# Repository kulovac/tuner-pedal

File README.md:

# Tuner Pedal

A tuner pedal project using an STM32 microcontroller with the CMSIS-DSP library

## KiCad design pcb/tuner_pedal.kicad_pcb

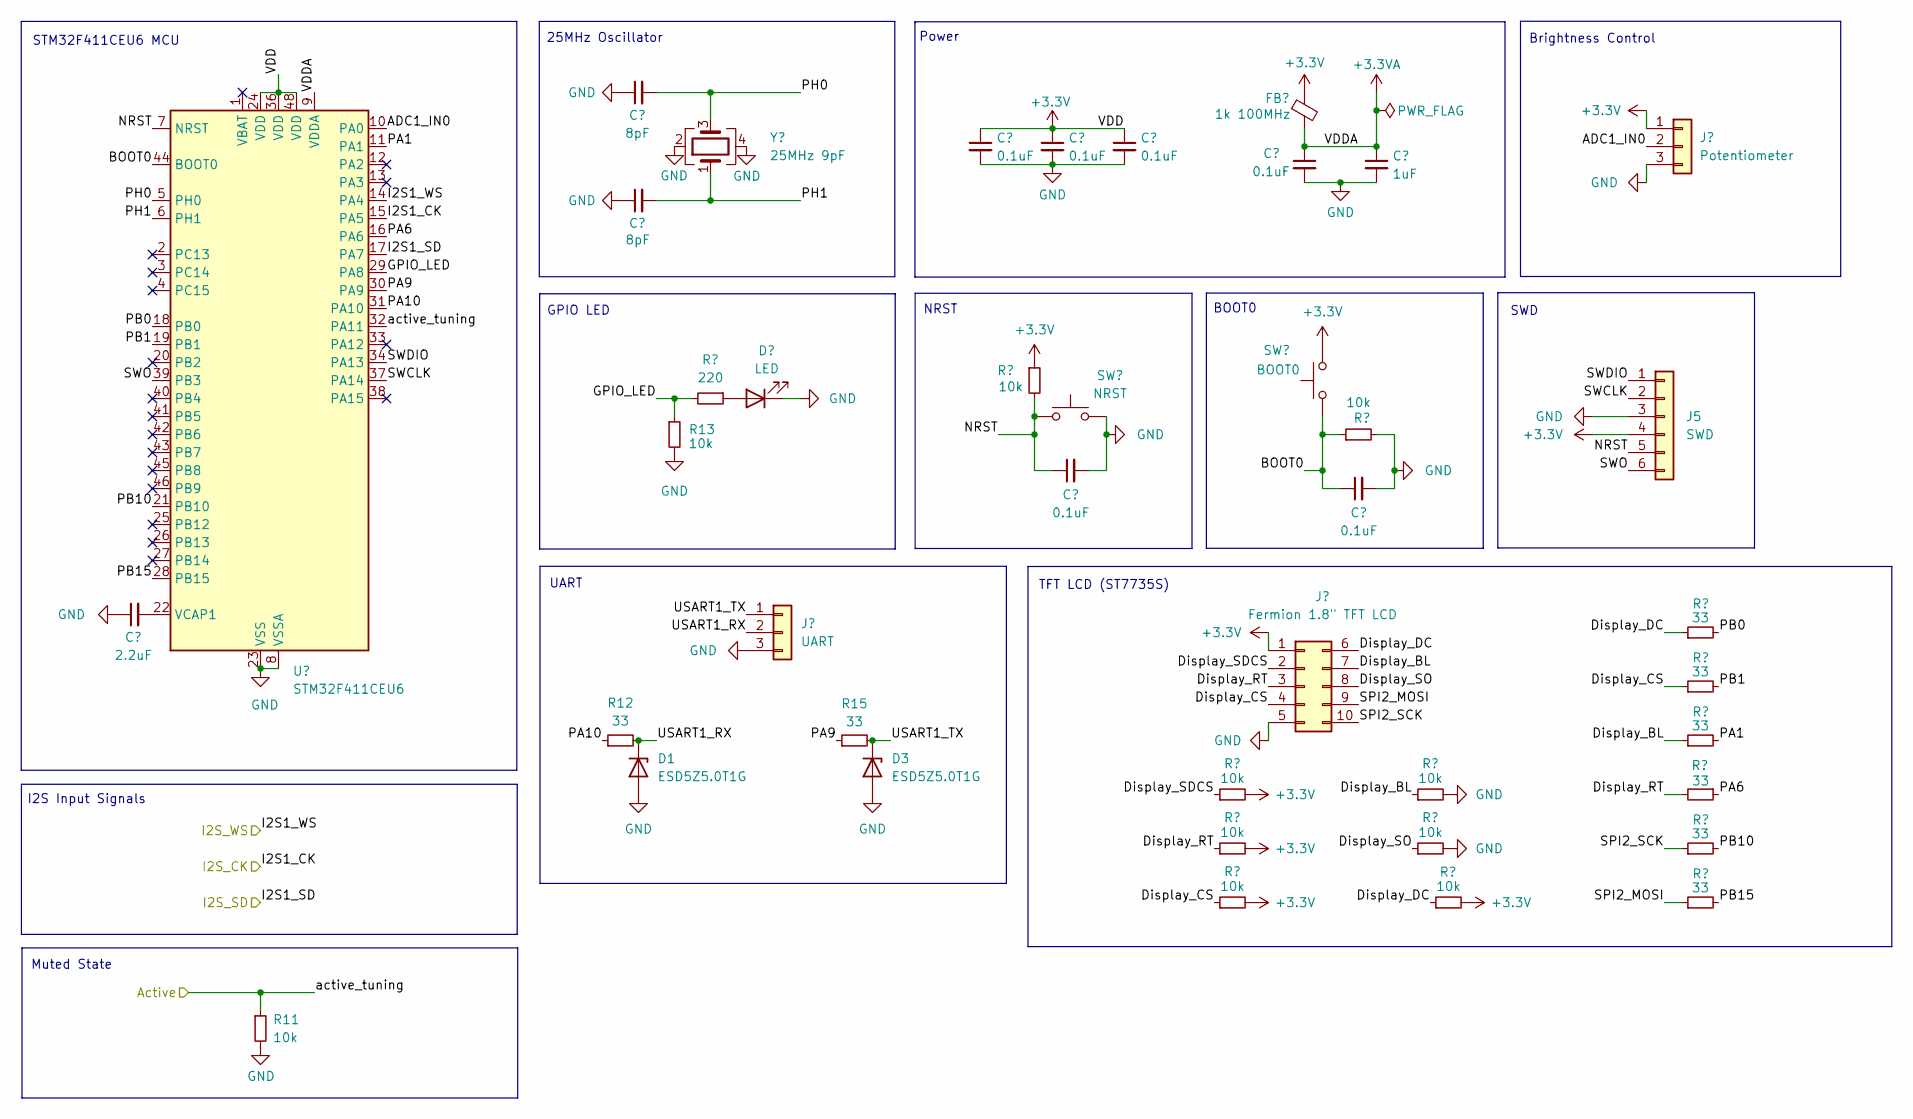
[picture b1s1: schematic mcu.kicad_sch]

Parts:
C22: 2.2uF; C_0805_2012Metric; MPN CL21B225KAFNNNE; LCSC C19110
C23, C24: 8pF; C_0402_1005Metric; MPN 0402CG8R0C500NT; LCSC C1578
C25, C26, C27, C28, C29, C30: 0.1uF; C_0402_1005Metric; MPN CL05B104KO5NNNC; LCSC C1525
C31: 1uF; C_0805_2012Metric; MPN CL21B105KAFNFNE; LCSC C1712
D1, D3: ESD5Z5.0T1G; D_SOD-523; MPN ESD5Z5.0T1G; LCSC C82044
D2: LED; LED_0603_1608Metric; MPN KT-0603R; LCSC C2286
FB1: 1k 100MHz; L_1806_4516Metric; MPN BLM41PG102SN1L; LCSC C88999
J3: UART; PinSocket_1x03_P2.54mm_Vertical
J4: Fermion 1.8" TFT LCD; PinHeader_2x05_P2.54mm_Vertical
J5: SWD; PinHeader_1x06_P2.54mm_Vertical
J6: Potentiometer; PinSocket_1x03_P2.54mm_Vertical
R11, R13, R16, R17, R18, R19, R20, R21, R22, R23: 10k; R_0603_1608Metric; MPN RC0603FR-0710KL; LCSC C98220
R12, R15, R24, R25, R26, R27, R28, R29: 33; R_0603_1608Metric; MPN RC0603FR-0733RL; LCSC C108661
R14: 220; R_0603_1608Metric; MPN RC0603FR-07220RL; LCSC C107696
SW1: NRST; SW_Push_1P1T_NO_6x6mm_H9.5mm; MPN TL3301AF160QG; LCSC C273519
SW2: BOOT0; SW_Push_1P1T_NO_6x6mm_H9.5mm; MPN TL3301AF160QG; LCSC C273519
U4: STM32F411CEU6; QFN-48-1EP_7x7mm_P0.5mm_EP5.6x5.6mm; MPN STM32F411CEU6; LCSC C60420
Y1: 25MHz 9pF; Crystal_SMD_3225-4Pin_3.2x2.5mm; MPN 3225-25-9-10-10/A; LCSC C2981679

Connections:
+3.3V: C25.1, C26.1, C28.1, FB1.1, J4.1, J5.4, J6.1, R16.1, R17.2, R18.2, R19.2, R23.2, SW2.2, U4.24 (VDD), U4.36 (VDD), U4.48 (VDD); also elsewhere on the board
+3.3VA: C29.1, C31.1, FB1.2, U4.9 (VDDA)
/MCU/ADC1_IN0: J6.2, U4.10 (PA0)
/MCU/BOOT0: C30.1, R20.1, SW2.1, U4.44 (BOOT0)
/MCU/Display_BL: J4.7, R21.1, R24.1
/MCU/Display_CS: J4.4, R19.1, R25.1
/MCU/Display_DC: J4.6, R23.1, R26.1
/MCU/Display_RT: J4.3, R18.1, R28.2
/MCU/Display_SDCS: J4.2, R17.1
/MCU/Display_SO: J4.8, R22.1
/MCU/GPIO_LED: R13.1, R14.2, U4.29 (PA8)
/MCU/I2S1_CK: U4.15 (PA5); also elsewhere on the board
/MCU/I2S1_SD: U4.17 (PA7); also elsewhere on the board
/MCU/I2S1_WS: U4.14 (PA4); also elsewhere on the board
/MCU/NRST: C27.1, J5.5, R16.2, SW1.1, U4.7 (NRST)
/MCU/PA1: R24.2, U4.11 (PA1)
/MCU/PA6: R28.1, U4.16 (PA6)
/MCU/PA9: R15.1, U4.30 (PA9)
/MCU/PA10: R12.1, U4.31 (PA10)
/MCU/PB0: R26.2, U4.18 (PB0)
/MCU/PB1: R25.2, U4.19 (PB1)
/MCU/PB10: R27.2, U4.21 (PB10)
/MCU/PB15: R29.2, U4.28 (PB15)
/MCU/PH0: C23.2, U4.5 (PH0), Y1.3
/MCU/PH1: C24.2, U4.6 (PH1), Y1.1
/MCU/SPI2_MOSI: J4.9, R29.1
/MCU/SPI2_SCK: J4.10, R27.1
/MCU/SWCLK: J5.2, U4.37 (PA14)
/MCU/SWDIO: J5.1, U4.34 (PA13)
/MCU/SWO: J5.6, U4.39 (PB3)
/MCU/USART1_RX: D1.1 (K), J3.2, R12.2
/MCU/USART1_TX: D3.1 (K), J3.1, R15.2
/MCU/active_tuning: R11.1, U4.32 (PA11); also elsewhere on the board
GND: C22.1, C23.1, C24.1, C25.2, C26.2, C27.2, C28.2, C29.2, C30.2, C31.2, D1.2 (A), D2.1 (K), D3.2 (A), J3.3, J4.5, J5.3, J6.3, R11.2, R13.2, R20.2, R21.2, R22.2, SW1.2, U4.8 (VSSA), U4.23 (VSS), U4.35 (VSS), U4.47 (VSS), U4.49 (VSS), Y1.2, Y1.4; also elsewhere on the board
unnamed: D2.2 (A), R14.1
unnamed: C22.2, U4.22 (VCAP1)

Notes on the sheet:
BOOT0
Muted State
NRST
TFT LCD (ST7735S)
GPIO LED
25MHz Oscillator
STM32F411CEU6 MCU
UART
SWD
Brightness Control
Power
I2S Input Signals

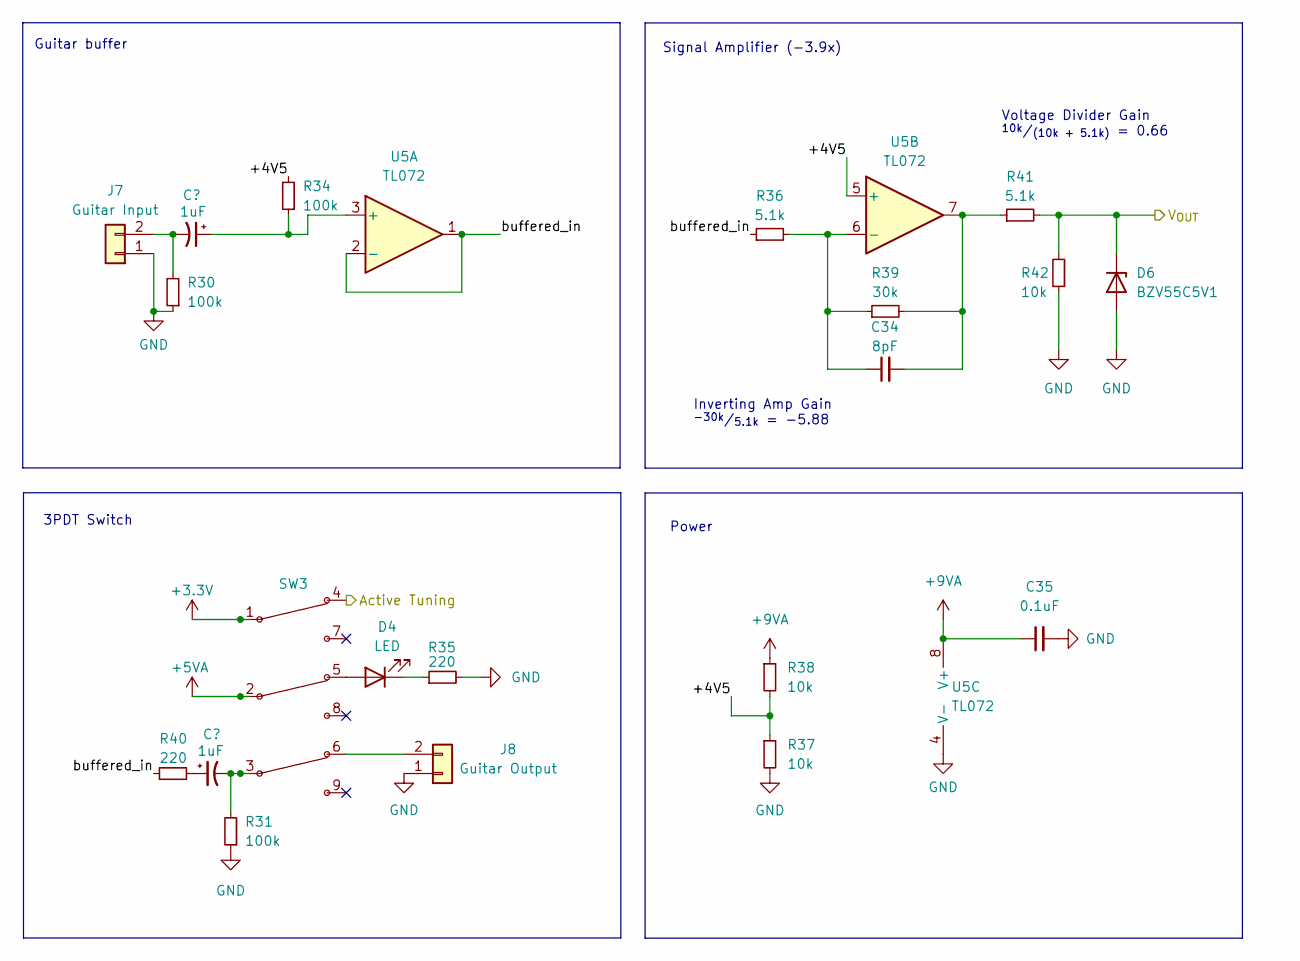
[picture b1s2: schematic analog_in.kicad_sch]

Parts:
C32, C33: 1uF; C_0805_2012Metric; MPN CL21B105KAFNFNE; LCSC C1712
C34: 8pF; C_0402_1005Metric; MPN 0402CG8R0C500NT; LCSC C1578
C35: 0.1uF; C_0402_1005Metric; MPN CL05B104KO5NNNC; LCSC C1525
D4: LED; PinHeader_1x02_P2.54mm_Vertical
D6: BZV55C5V1; D_MiniMELF; MPN BZV55B5V1; LCSC C545327
J7: Guitar Input; PinSocket_1x02_P2.54mm_Vertical
J8: Guitar Output; PinSocket_1x02_P2.54mm_Vertical
R30, R31, R34: 100k; R_0603_1608Metric; MPN RC0603FR-07100KL; LCSC C14675
R35, R40: 220; R_0603_1608Metric; MPN RC0603FR-07220RL; LCSC C107696
R36: 5.1k; R_Axial_DIN0207_L6.3mm_D2.5mm_P7.62mm_Horizontal; MPN MFR-25FTE52-5K1; LCSC C173033
R37, R38, R42: 10k; R_0603_1608Metric; MPN RC0603FR-0710KL; LCSC C98220
R39: 30k; R_Axial_DIN0207_L6.3mm_D2.5mm_P7.62mm_Horizontal; MPN MFR-25FTE52-30K; LCSC C173003
R41: 5.1k; R_0603_1608Metric; MPN RC0603FR-075K1L; LCSC C105580
SW3: PinHeader_2x03_P2.54mm_Vertical
U5: TL072; DIP-8_W7.62mm_Socket

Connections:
+3.3V: SW3.1; also elsewhere on the board
+5VA: SW3.2; also elsewhere on the board
+9VA: C35.1, R38.1, U5.8 (V+); also elsewhere on the board
/ADC/V_{IN}: D6.1 (K), R41.2, R42.2; also elsewhere on the board
/Analog Signal/+4V5: R34.2, R37.1, R38.2, U5.5 (+); also elsewhere on the board
/Analog Signal/buffered_in: R36.1, R40.1, U5.1, U5.2 (-)
/MCU/active_tuning: SW3.4; also elsewhere on the board
GND: C35.2, D6.2 (A), J7.1, J8.1, R30.1, R31.1, R35.2, R37.2, R42.1, U5.4 (V-); also elsewhere on the board
unnamed: C33.1, R40.2
unnamed: C33.2, R31.2, SW3.3
unnamed: C34.2, R39.2, R41.1, U5.7
unnamed: D4.2 (A), SW3.5
unnamed: D4.1 (K), R35.1
unnamed: C32.2, J7.2, R30.2
unnamed: J8.2, SW3.6
unnamed: C32.1, R34.1, U5.3 (+)
unnamed: C34.1, R36.2, R39.1, U5.6 (-)

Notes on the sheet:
Power
3PDT Switch
Inverting Amp Gain ^{-30k}/_{5.1k} = -5.88
Voltage Divider Gain ^{10k}/_{(10k + 5.1k)} = 0.66
Guitar buffer
Signal Amplifier (-3.9x)

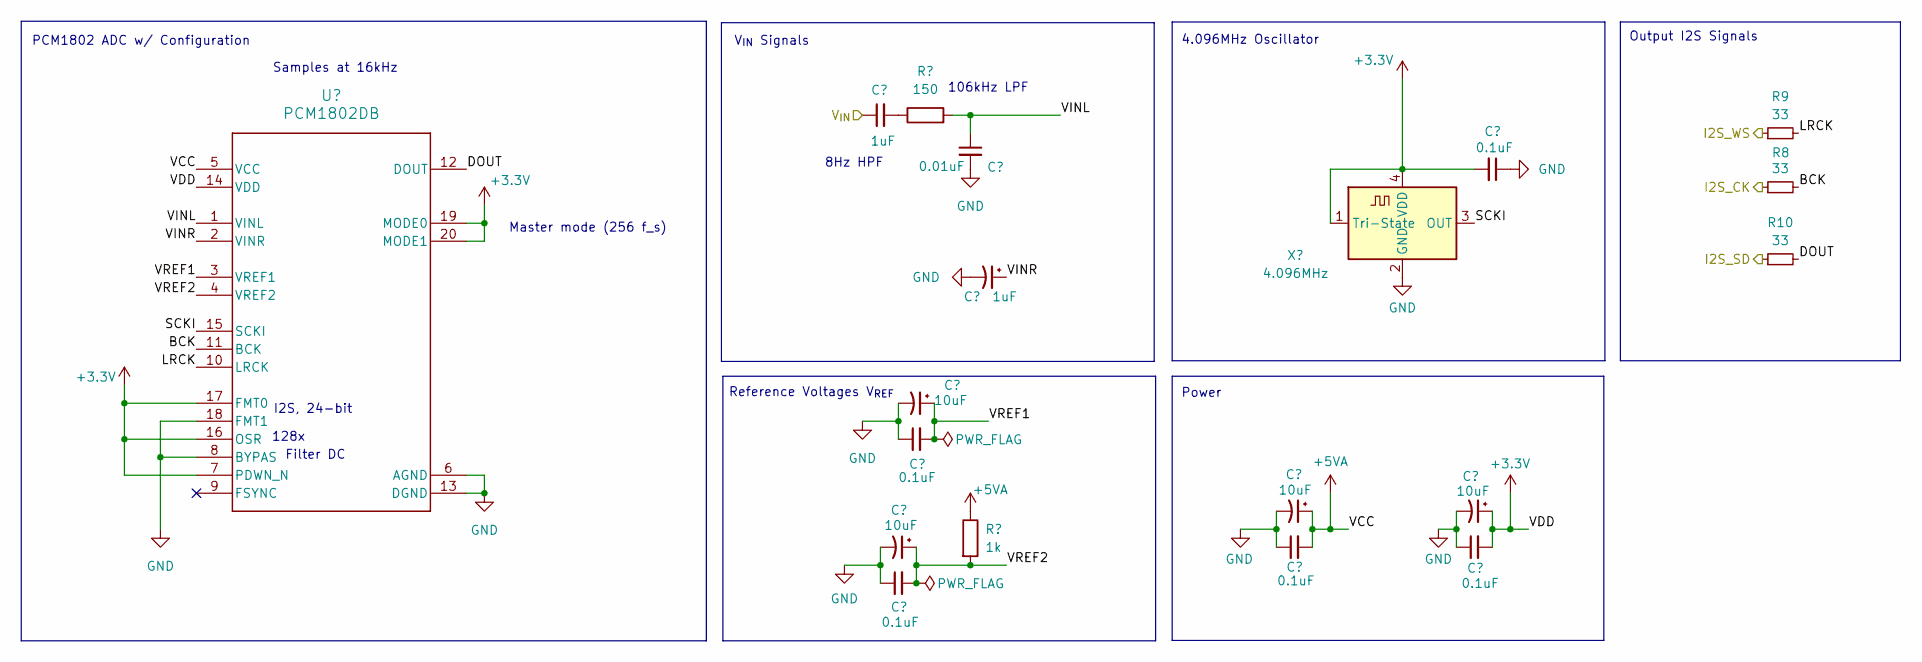
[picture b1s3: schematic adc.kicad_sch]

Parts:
C10, C16: 1uF; C_0805_2012Metric; MPN CL21B105KAFNFNE; LCSC C1712
C11, C13, C17, C20: 10uF; CP_EIA-3216-18_Kemet-A; MPN TAJA106K010RNJ; LCSC C7177
C12, C14, C18, C19, C21: 0.1uF; C_0402_1005Metric; MPN CL05B104KO5NNNC; LCSC C1525
C15: 0.01uF; C_0603_1608Metric; MPN CL10C100JB8NNNC; LCSC C1634
R6: 150; R_0603_1608Metric; MPN RC0603FR-07150RL; LCSC C114608
R7: 1k; R_0603_1608Metric; MPN RC0603JR-071KL; LCSC C14676
R8, R9, R10: 33; R_0603_1608Metric; MPN RC0603FR-0733RL; LCSC C108661
U3: PCM1802DB; SSOP-20_5.3x7.2mm_P0.65mm; MPN PCM1802DB; LCSC C1520787
X1: 4.096MHz; Crystal_SMD_3225-4Pin_3.2x2.5mm; MPN OT32254.096MJBA4SL; LCSC C2831395

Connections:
+3.3V: C19.2, C20.1, C21.2, U3.7 (PDWN_N), U3.14 (VDD), U3.16 (OSR), U3.17 (FMT0), U3.19 (MODE0), U3.20 (MODE1), X1.1 (Tri-State), X1.4 (VDD); also elsewhere on the board
+5VA: C17.1, C18.2, R7.1, U3.5 (VCC); also elsewhere on the board
/ADC/BCK: R8.2, U3.11 (BCK)
/ADC/DOUT: R10.2, U3.12 (DOUT)
/ADC/LRCK: R9.2, U3.10 (LRCK)
/ADC/SCKI: U3.15 (SCKI), X1.3 (OUT)
/ADC/VINL: C15.1, R6.2, U3.1 (VINL)
/ADC/VINR: C16.1, U3.2 (VINR)
/ADC/VREF1: C13.1, C14.2, U3.3 (VREF1)
/ADC/VREF2: C11.1, C12.2, R7.2, U3.4 (VREF2)
/ADC/V_{IN}: C10.1; also elsewhere on the board
/MCU/I2S1_CK: R8.1; also elsewhere on the board
/MCU/I2S1_SD: R10.1; also elsewhere on the board
/MCU/I2S1_WS: R9.1; also elsewhere on the board
GND: C11.2, C12.1, C13.2, C14.1, C15.2, C16.2, C17.2, C18.1, C19.1, C20.2, C21.1, U3.6 (AGND), U3.8 (BYPAS), U3.13 (DGND), U3.18 (FMT1), X1.2 (GND); also elsewhere on the board
unnamed: C10.2, R6.1

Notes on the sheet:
I2S, 24-bit
Master mode (256 f_s)
4.096MHz Oscillator
PCM1802 ADC w/ Configuration
Output I2S Signals
Reference Voltages V_{REF}
Samples at 16kHz
8Hz HPF
Filter DC
106kHz LPF
128x
Power
V_{IN} Signals

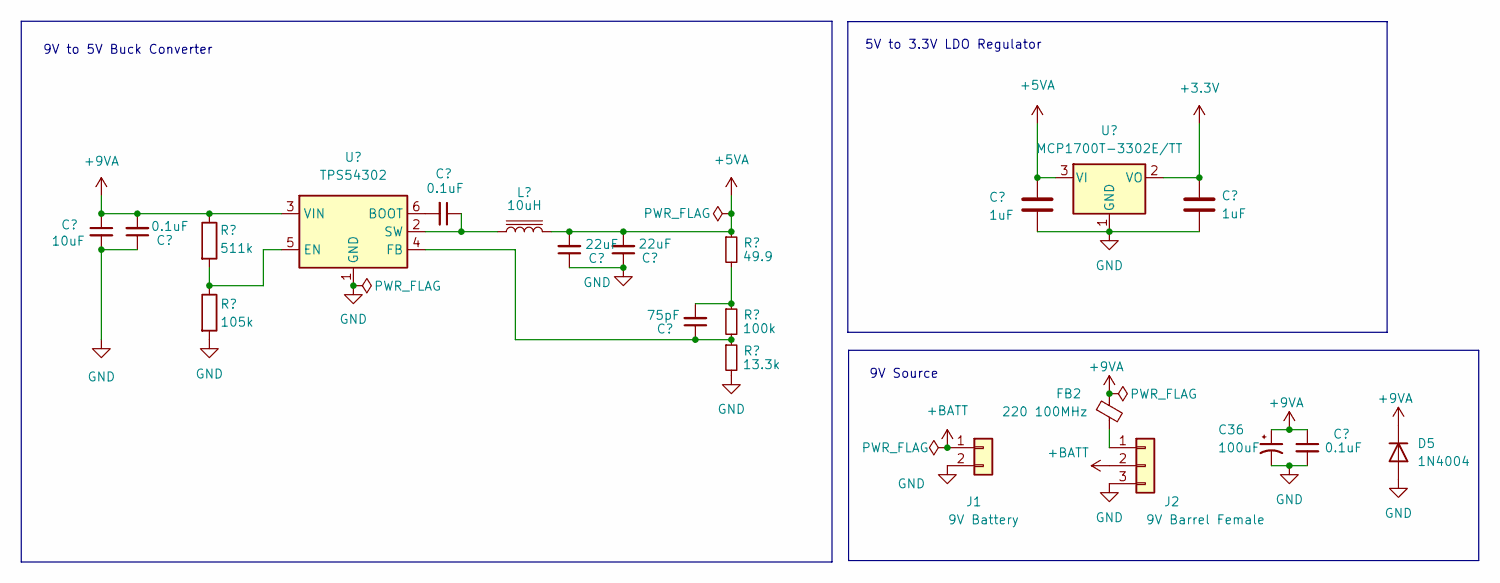
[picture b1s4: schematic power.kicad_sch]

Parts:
C1: 10uF; C_1206_3216Metric; MPN CC1206KKX7R8BB106; LCSC C70462
C2, C3, C9: 0.1uF; C_0402_1005Metric; MPN CL05B104KO5NNNC; LCSC C1525
C4, C5: 22uF; C_1206_3216Metric; MPN GRM31CR71A226KE15L; LCSC C91604
C6: 75pF; C_0402_1005Metric; MPN CC0402JRNPO9BN750; LCSC C107010
C7, C8: 1uF; C_0805_2012Metric; MPN CL21B105KAFNFNE; LCSC C1712
C36: 100uF; CP_Elec_6.3x5.4; MPN RVT100UF16V67RV0016; LCSC C2887276
D5: 1N4004; D_DO-41_SOD81_P10.16mm_Horizontal; MPN 1N4004; LCSC C3058
FB2: 220 100MHz; L_0603_1608Metric; MPN BLM18PG221SN1D; LCSC C80165
J1: 9V Battery; PinSocket_1x02_P2.54mm_Vertical
J2: 9V Barrel Female; PinHeader_1x03_P2.54mm_Vertical
L1: 10uH; L_6.3x6.3_H3; MPN PNLS6045-100M 10UH; LCSC C2849537
R1: 511k; R_0603_1608Metric; MPN RC0603FR-07511KL; LCSC C188257
R2: 105k; R_0603_1608Metric; MPN RC0603FR-07105KL; LCSC C141685
R3: 49.9; R_0603_1608Metric; MPN RC0603FR-0749R9L; LCSC C114625
R4: 100k; R_0603_1608Metric; MPN RC0603FR-07100KL; LCSC C14675
R5: 13.3k; R_0603_1608Metric; MPN RC0603FR-0713K3L; LCSC C185373
U1: TPS54302; SOT-23-6; MPN TPS54302DDCR; LCSC C311983
U2: MCP1700T-3302E/TT; SOT-23-3; MPN MCP1700T-3302E/TT; LCSC C39051

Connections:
+3.3V: C8.1, U2.2 (VO); also elsewhere on the board
+5VA: C4.2, C5.2, C7.1, L1.2, R3.1, U2.3 (VI); also elsewhere on the board
+9VA: C1.1, C2.2, C9.1, C36.1, D5.1 (K), FB2.1, R1.1, U1.3 (VIN); also elsewhere on the board
+BATT: J1.1, J2.2
GND: C1.2, C2.1, C4.1, C5.1, C7.2, C8.2, C9.2, C36.2, D5.2 (A), J1.2, J2.3, R2.2, R5.2, U1.1 (GND), U2.1 (GND); also elsewhere on the board
unnamed: C6.2, R3.2, R4.1
unnamed: FB2.2, J2.1
unnamed: C3.2, U1.6 (BOOT)
unnamed: R1.2, R2.1, U1.5 (EN)
unnamed: C6.1, R4.2, R5.1, U1.4 (FB)
unnamed: C3.1, L1.1, U1.2 (SW)

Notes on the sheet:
9V Source
5V to 3.3V LDO Regulator
9V to 5V Buck Converter

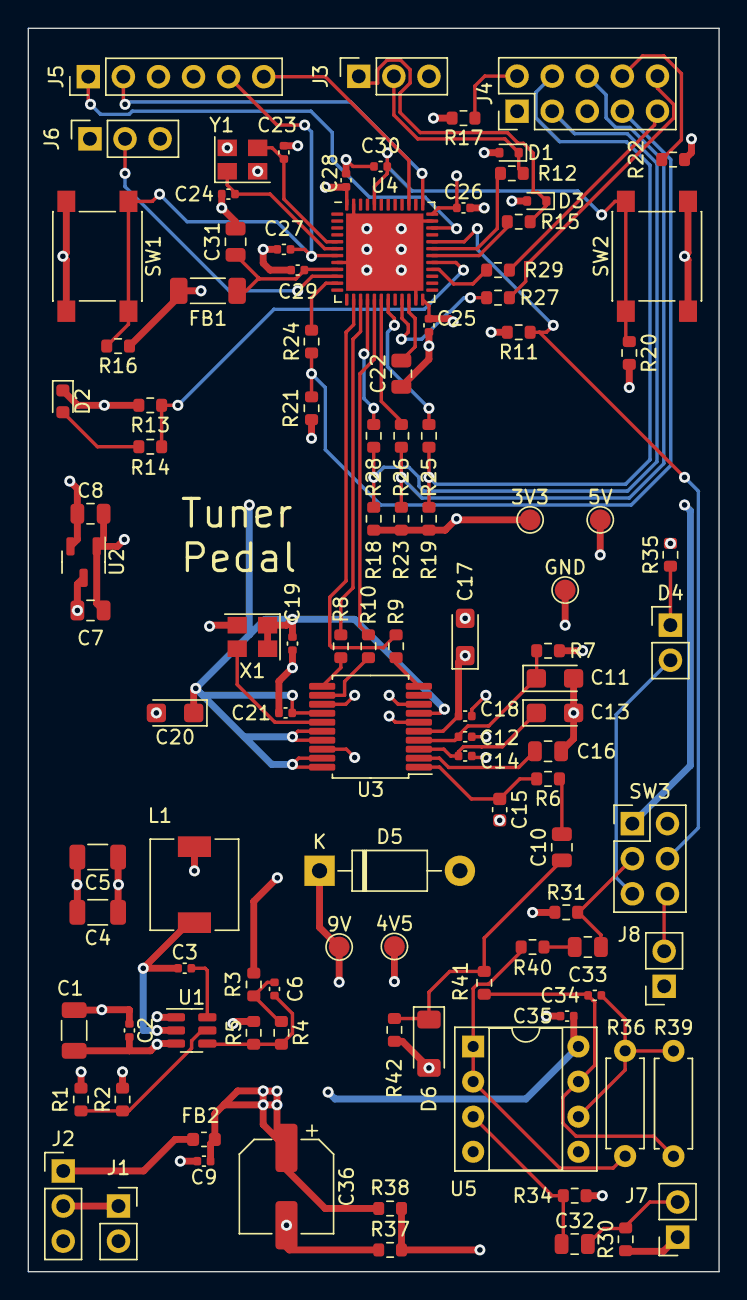
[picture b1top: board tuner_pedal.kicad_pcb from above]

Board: 4 copper layers, 50.0 x 90.0 mm, 108 parts (0 on the bottom side), 66 nets.

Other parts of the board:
3V3, 4V5, 5V, 9V: TestPoint_Pad_D1.5mm
GND: TestPoint_Pad_D1.5mm

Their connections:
+3.3V: 3V3.1; also elsewhere on the board
+5VA: 5V.1; also elsewhere on the board
+9VA: 9V.1; also elsewhere on the board
/Analog Signal/+4V5: 4V5.1; also elsewhere on the board
GND: GND.1; also elsewhere on the board

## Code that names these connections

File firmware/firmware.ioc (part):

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Mcu.Name=STM32F411C(C-E)Ux
Mcu.Package=UFQFPN48
Mcu.UserName=STM32F411CEUx
PA0-WKUP.Signal=ADCx_IN0
PA1.Signal=S_TIM2_CH2
PA10.Mode=Asynchronous
PA10.Signal=USART1_RX
PA11.Signal=GPIO_Input
PA13.Signal=SYS_JTMS-SWDIO
PA14.Signal=SYS_JTCK-SWCLK
PA4.Mode=Half_Duplex_Slave
PA4.Signal=I2S1_WS
PA5.Mode=Half_Duplex_Slave
PA5.Signal=I2S1_CK
PA6.Signal=GPIO_Output
PA7.Mode=Half_Duplex_Slave
PA7.Signal=I2S1_SD
PA8.Signal=GPIO_Output
PA9.Mode=Asynchronous
PA9.Signal=USART1_TX
PB0.Signal=GPIO_Output
PB1.Signal=GPIO_Output
PB10.Mode=TX_Only_Simplex_Unidirect_Master
PB10.Signal=SPI2_SCK
PB15.Mode=TX_Only_Simplex_Unidirect_Master
PB15.Signal=SPI2_MOSI
PB3.Signal=SYS_JTDO-SWO
RCC.HSE_VALUE=25000000
RCC.SYSCLKFreq_VALUE=16000000
board=custom

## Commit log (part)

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2024-09-09 Initial commit for tuner pedal
2024-09-09 Added README
2024-09-10 reformatted main
2024-09-10 added a note and cent finder for the tuner
2024-09-10 now says cts when getting note
2025-05-09 Initial commit - set up python directory for alg testing
2025-06-13 first iteration of cmsis dsp yin algorithm
2025-06-20 Updated gitignore for KiCAD
2025-06-20 Added 5->3.3V LDO
2025-06-20 Starting tuner pedal schematic with ADC
2025-06-20 Added 9V->5V buck converter
2025-06-20 added githubs gitignore for kicad
2025-06-20 Adding tables for local components
2025-06-20 Added crystal oscillators to stm32
2025-06-20 added AC coupling cap to unused V_inR
2025-06-20 Deleted unused component
2025-06-20 Removed RTC crystal
2025-06-20 Connected stm32 to 3V3
2025-06-20 Added SWD header
2025-06-20 Defined which pins will be used on the stm32
2025-06-20 Defined headers for each interface
2025-06-21 Added GPIO attached LED for debugging purposes
2025-06-21 Made FSYNC floating
2025-06-21 Added NRST and BOOT0 buttons
2025-06-21 Added pull-ups/downs and series termination to LCD
2025-06-23 Added pot pins
2025-06-23 Created a power sheet
2025-06-23 Added filtering cap to 9V barrel
2025-06-24 Removed power hierarchy labels
2025-06-24 Made sheet for ADC
2025-06-24 Made MCU sheet
2025-06-24 Connected SWO pin
2025-06-25 Changed the LPF to 106 kHz cutoff
2025-06-27 Created 3PDT footswitch schematic symbol
2025-06-27 Created analog frontend
2025-06-27 Changed cap to nonpolarized to account for analog_in biasing scheme
2025-06-27 Added input GPIO to check muted state
2025-06-27 Brought in analog frontend
2025-06-27 Fixed I/O direction on hierarchy labels
2025-06-27 Reordered components
2025-06-27 Connected VDD cap to GND
2025-06-27 formatting
2025-06-27 actually connect net
2025-06-27 Adding safety to output jack signal path
2025-06-27 Attached backlight to timer capable pin
2025-06-28 Assigned footprints and jlcpcb part number to all components
2025-06-29 Added correct datasheet to pcm1802 symbol
2025-06-29 Changed 10k inverting amp resistor to THT for easy swapping
2025-06-29 Changed op amp supply to 9V to make sure clipping doesn't occur
2025-06-29 Added better filtering for 9V supply
2025-06-29 ERC fixes
2025-06-29 Starting PCB layout
2025-06-30 Added Analog in signal and 9V to 5V buck converter
2025-07-01 First revision of the pcb layout
2025-07-02 trying to isolate analog from noise sources
2025-07-02 Moved LED to make soldering a bit easier
2025-07-11 Updated gitignore for C and STM32
2025-07-11 Generated template for firmware
2025-07-11 cloned 'https://github.com/bersch/ST7735S.git'
2025-07-11 Configured ST7735S library to correct pins
2025-07-11 cloned 'https://github.com/ARM-software/CMSIS-DSP.git'
2025-07-12 Deleted unnecessary files
2025-07-28 Lowered resistor values and added protection diode
2025-08-25 Created I2S connection
2025-08-25 Basic uart logging for dev work
2026-06-27 Starting to cleanup firmware structure
